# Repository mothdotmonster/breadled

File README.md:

# BREADLED

BREADLED is a breakout board for WS2812 addressable LEDs, designed to fit perfectly into common breadboards and perfboard without taking up an excessive amount of space.

PINOUT:

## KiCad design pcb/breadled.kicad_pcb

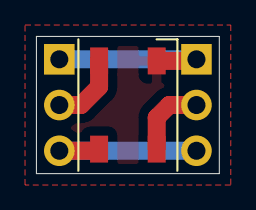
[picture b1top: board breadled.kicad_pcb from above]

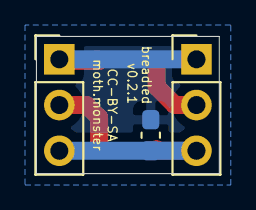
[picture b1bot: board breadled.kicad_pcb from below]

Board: 2 copper layers, 10.2 x 7.6 mm, 4 parts (3 on the bottom side), 4 nets.

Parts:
C1: 104; C_0603_1608Metric_Pad1.08x0.95mm_HandSolder
D1: WS2812B; LED_WS2812B_PLCC4_5.0x5.0mm_P3.2mm
J1, J2: Conn_01x03_Male; PinHeader_1x03_P2.54mm_Vertical

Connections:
/5V: C1.1, D1.1, J1.3, J2.3
/GND: C1.2, D1.3, J1.1, J2.1
unnamed: D1.2, J2.2
unnamed: D1.4, J1.2

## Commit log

2022-03-01 add pinout
2023-06-27 better pinout diagram

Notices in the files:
pcb/breadled.kicad_pcb:
CC-BY-SA
